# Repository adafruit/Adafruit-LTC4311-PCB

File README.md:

## Adafruit LTC4311 I2C Extender / Active Terminator PCB

<a href="http://www.adafruit.com/products/4756"><br/>
Click here to purchase one from the Adafruit shop</a>

PCB files for the Adafruit LTC4311 I2C Extender / Active Terminator.

Format is EagleCAD schematic and board layout
* https://www.adafruit.com/product/4756

### Description

I2C stands for Inter-Integrated-Circuit communications, its meant for short distances on a PCB or subassembly. But, hey, we're engineers and we like to push the limits of technology, right? So why not try to have I2C run over a meter long cable, or even longer? Well, if you try to do that you'll quickly find that the length of the cable adds capacitance and resistance that slows down the open-drain pullups used in I2C, making it hard to use 100KHz+ clock speeds. You could try slowing down your I2C clock to 1 KHz...or you could use an Adafruit LTC4311 active terminator like this one!

Using this board is easy: connect it to your I2C bus at the beginning of the chain (if you don't have a massively long cable, you can also try at the end of the chain). When the chip is powered and enabled, it will watch the SCL and SDA lines. When it sees them being pulled up through the I2C resistors, it will activate and dump in some current to give it a boost thru to the top power rail.

You can now achieve much faster data rates without having to noodle with resistors, and over long cables. We ran a 400 KHz OLED over 3 meters of phone wire with ease. With a 100KHz signal, we even ran a BME680 over 100 feet of Ethernet (about 3000pF round trip!), and had an OLED display the sensor details.

Runs with any bus voltage, from 1.6V to 5.5V and up to 400 KHz SCL speed, with cables up to 4000pF. No special firmware, software, or configuration required. Simply plug the power, ground, SCL and SDA connectors into your bus and watch as your rise times magically turn sawtooths into square waves.

To get you going fast, we spun up a custom made PCB in the STEMMA QT form factor, making it easy to interface with. The STEMMA QT connectors on either side are compatible with the SparkFun Qwiic I2C connectors. This allows you to make solderless connections between your development board and the LTC4311 or to chain it with a wide range of other sensors and accessories using a compatible cable.

### License

Adafruit invests time and resources providing this open source design, please support Adafruit and open-source hardware by purchasing products from [Adafruit](https://www.adafruit.com)!

Designed by Limor Fried/Ladyada for Adafruit Industries.

Creative Commons Attribution/Share-Alike, all text above must be included in any redistribution.
See license.txt for additional details.

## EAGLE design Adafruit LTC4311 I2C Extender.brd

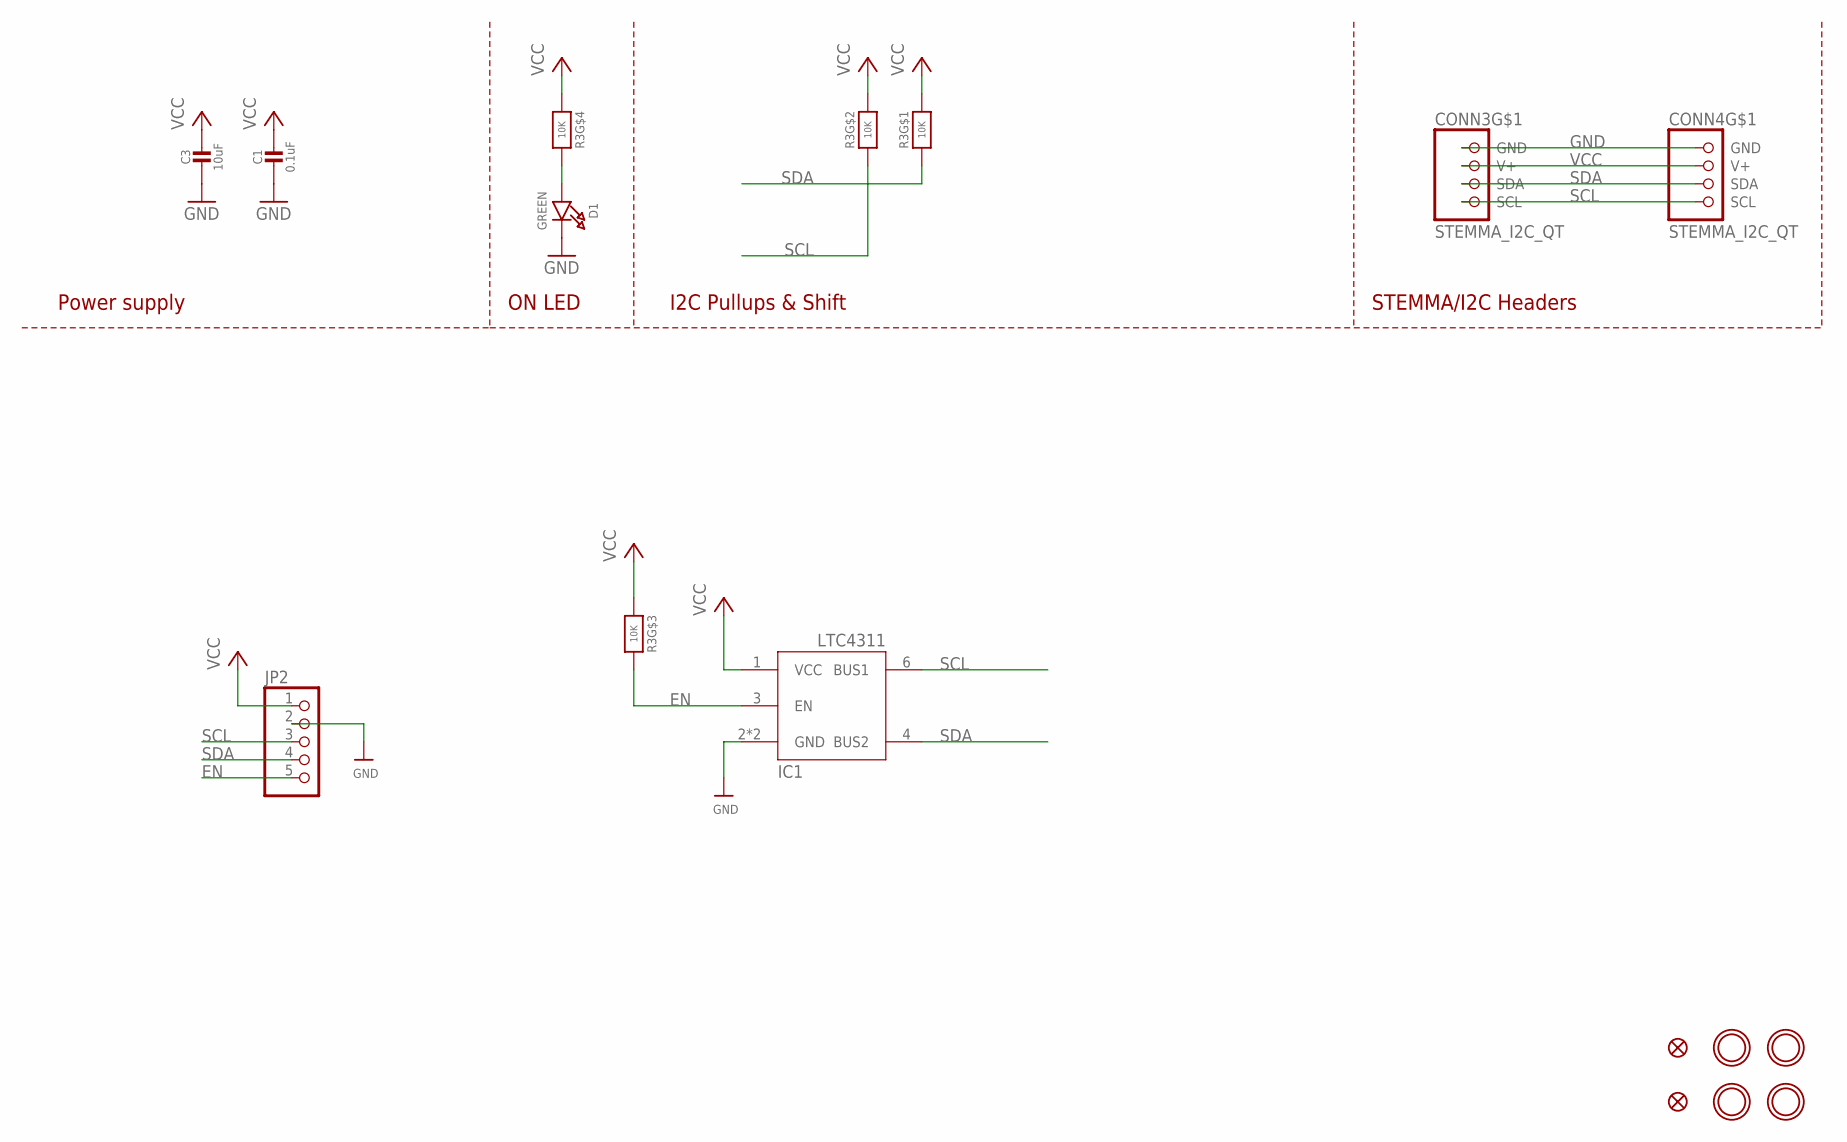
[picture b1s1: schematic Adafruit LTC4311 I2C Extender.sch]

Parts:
C1: 0.1uF; 0603-NO
C3: 10uF; 0805-NO
CONN3, CONN4: STEMMA_I2C_QT; JST_SH4
D1: GREEN; CHIPLED_0603_NOOUTLINE
FID3, FID4: FIDUCIAL_1MM
IC1: LTC4311_SC70; SC70-6L
JP2: HEADER-1X570MIL; 1X05_ROUND_70
R3: 10K; RESPACK_4X0603
U$1, U$17, U$19, U$21: MOUNTINGHOLE2.5; MOUNTINGHOLE_2.5_PLATED

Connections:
EN: IC1.3 (EN), JP2.5, R3.6 (2)
GND: C1.2, C3.2, CONN3.1 (GND), CONN4.1 (GND), D1.C, IC1.2 (GND), IC1.5 (GND), JP2.2
unnamed: D1.A, R3.5 (2)
SCL: CONN3.4 (SCL), CONN4.4 (SCL), IC1.6 (BUS1), JP2.3, R3.2 (1)
SDA: CONN3.3 (SDA), CONN4.3 (SDA), IC1.4 (BUS2), JP2.4, R3.1
VCC: C1.1, C3.1, CONN3.2 (V+), CONN4.2 (V+), IC1.1 (VCC), JP2.1, R3.3 (1), R3.4 (1), R3.7 (2), R3.8 (2)

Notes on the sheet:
I2C Pullups & Shift
STEMMA/I2C Headers
ON LED
Power supply

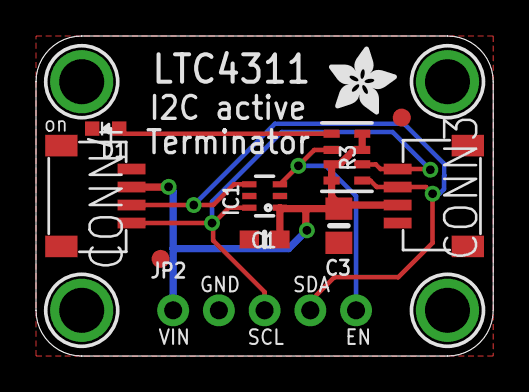
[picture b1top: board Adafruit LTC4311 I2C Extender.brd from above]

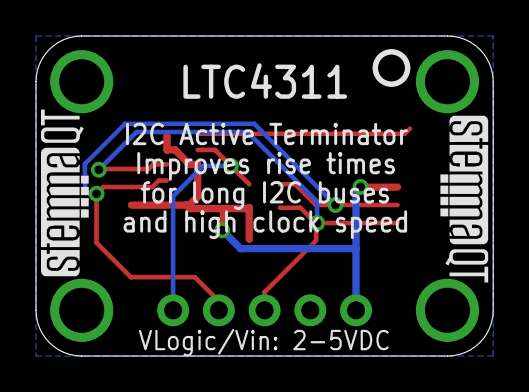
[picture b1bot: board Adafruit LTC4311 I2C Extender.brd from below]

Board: 2 copper layers, 25.4 x 17.8 mm, 18 parts (3 on the bottom side), 6 nets.

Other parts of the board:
U$22: ADAFRUIT_3.5MM
U$25: PCBFEAT-REV-040
U$30, U$31: STEMMAQT

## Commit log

2020-09-30 Adding board files.

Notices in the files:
parts and their libraries:
microbuilder: This work is placed in the public domain, and may be freely used for commercial and non-commercial work with the following conditions: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
